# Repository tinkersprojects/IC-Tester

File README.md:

# IC Tester
[https://tinkersprojects.com/](https://tinkersprojects.com/)

This is an IC tester for any type of logic chip. The device pules every pin combination and reads the all other pins to find which type of chip it is. The chip would have been already analysed before testing.

To read a 28 pin chip would take about 1/2 days and Thisbe is why I made the device be able to select the number pins of the chip to Be Tested. The larger the number of pins the slower it will read.

The device USB a sheld that attaches to an Arduino mega development board. The sheld has an LCD, SD and a user interface as well as the chip reader. To test the chip, the device uses 5v from the Arduino.

The PCB can be purchased from https://tinkersprojects.com/product/ic-tester/

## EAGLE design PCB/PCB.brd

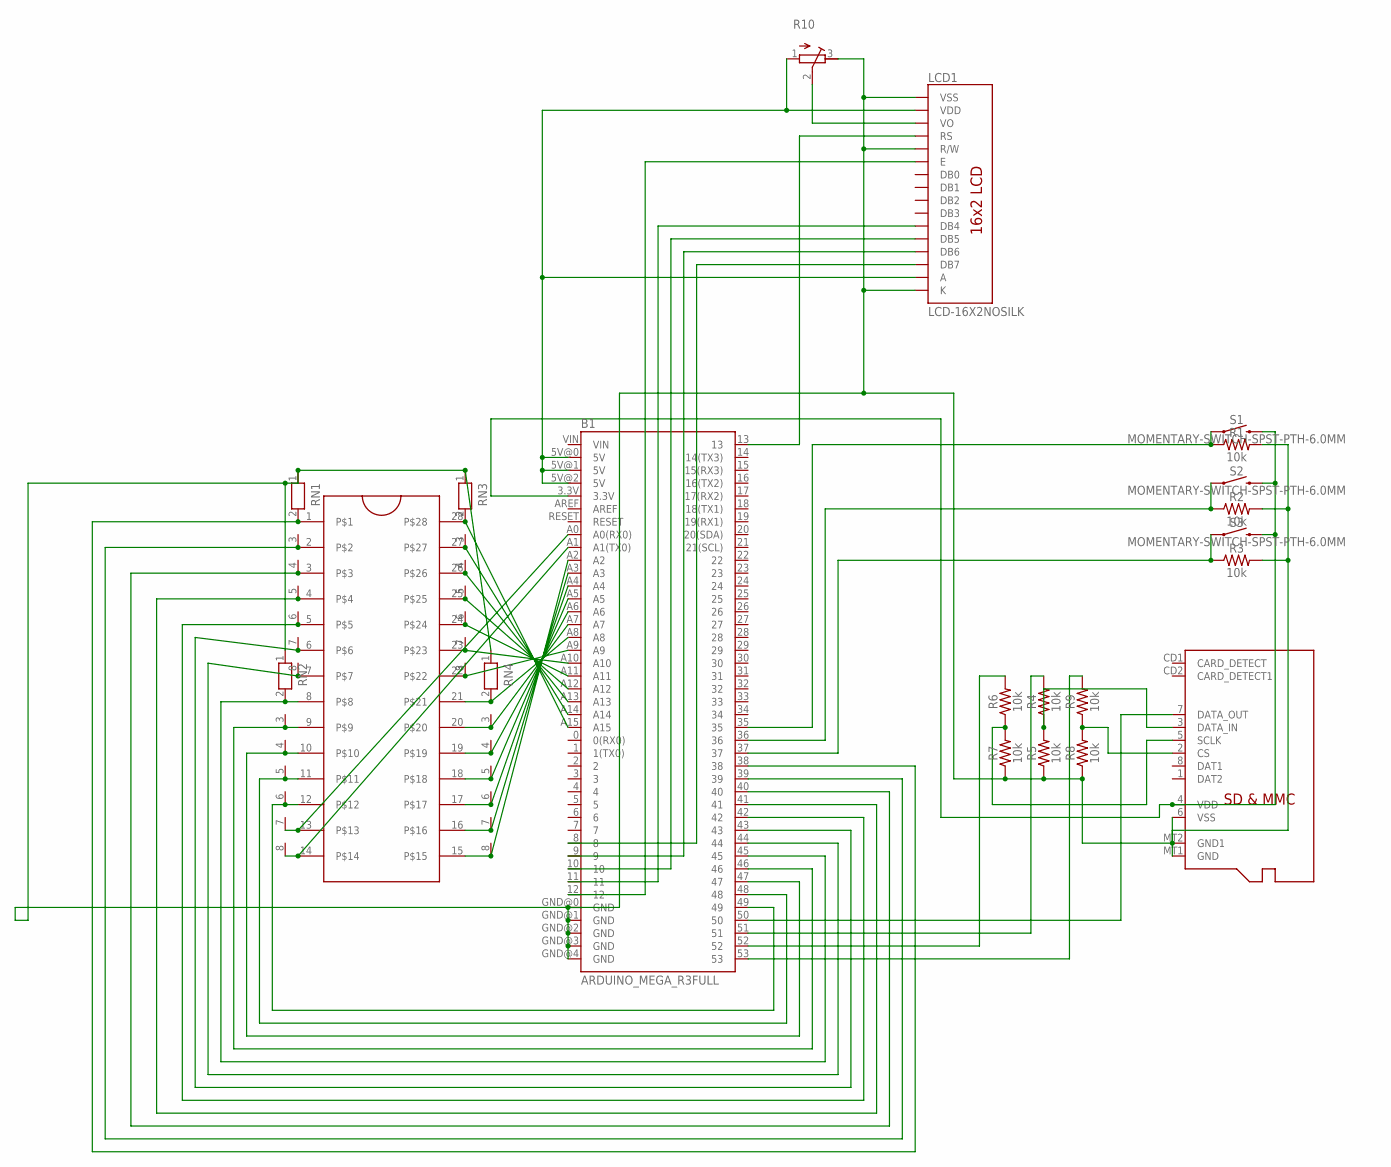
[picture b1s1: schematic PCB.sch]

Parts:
B1: ARDUINO_MEGA_R3FULL; ARDUINO_MEGA
LCD1: LCD-16X2NOSILK; LCD-16X2_NOSILK
R1, R2, R3, R4, R5, R6, R7, R8, R9: 10k; AXIAL-0.3
R10: R-TRIMM3339P; RTRIM3339P
RN1, RN2, RN3, RN4: RN07; RN-8
S1, S2, S3: MOMENTARY-SWITCH-SPST-PTH-6.0MM; TACTILE_SWITCH_PTH_6.0MM
U$1: MICROSD
U$2: ZIFSOCKET-28-3ZIFFSOCKET-28-3; DIL28-3-ZIF_SOCKET

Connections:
unnamed: B1.A15, RN3.2, U$2.28
unnamed: B1.A14, RN3.3, U$2.27
unnamed: B1.A13, RN3.4, U$2.26
unnamed: B1.A12, RN3.5, U$2.25
unnamed: B1.A11, RN3.6, U$2.24
unnamed: B1.A10, RN3.7, U$2.23
unnamed: B1.A9, RN3.8, U$2.22
unnamed: B1.A8, RN4.2, U$2.21
unnamed: B1.A7, RN4.3, U$2.20
unnamed: B1.A6, RN4.4, U$2.19
unnamed: B1.A5, RN4.5, U$2.18
unnamed: B1.A4, RN4.6, U$2.17
unnamed: B1.A3, RN4.7, U$2.16
unnamed: B1.A2, RN4.8, U$2.15
unnamed: B1.A1 (A1(TX0)), RN2.8, U$2.14
unnamed: B1.A0 (A0(RX0)), RN2.7, U$2.13
unnamed: B1.49, RN2.6, U$2.12
unnamed: B1.48, RN2.5, U$2.11
unnamed: B1.47, RN2.4, U$2.10
unnamed: B1.46, RN2.3, U$2.9
unnamed: B1.45, RN2.2, U$2.8
unnamed: B1.44, RN1.8, U$2.7
unnamed: B1.43, RN1.7, U$2.6
unnamed: B1.42, RN1.6, U$2.5
unnamed: B1.41, RN1.5, U$2.4
unnamed: B1.40, RN1.4, U$2.3
unnamed: B1.39, RN1.3, U$2.2
unnamed: B1.38, RN1.2, U$2.1
unnamed: B1.37, R3.P$1 (1), S3.1
unnamed: B1.5V@0 (5V), B1.5V@1 (5V), B1.5V@2 (5V), LCD1.2 (VDD), LCD1.15 (A), R10.1 (A)
unnamed: R6.P$1 (1), R7.P$2 (2), U$1.5 (SCLK)
unnamed: R8.P$2 (2), R9.P$1 (1), U$1.2 (CS)
unnamed: LCD1.3 (VO), R10.2 (S)
unnamed: B1.50, U$1.7 (DATA_OUT)
unnamed: R4.P$1 (1), R5.P$2 (2), U$1.3 (DATA_IN)
unnamed: B1.51, R4.P$2 (2)
unnamed: B1.53, R9.P$2 (2)
unnamed: B1.52, R6.P$2 (2)
unnamed: B1.13, LCD1.4 (RS)
unnamed: B1.12, LCD1.6 (E)
unnamed: B1.11, LCD1.11 (DB4)
unnamed: B1.10, LCD1.12 (DB5)
unnamed: B1.9, LCD1.13 (DB6)
unnamed: B1.8, LCD1.14 (DB7)
unnamed: B1.36, R2.P$1 (1), S2.1
unnamed: B1.35, R1.P$1 (1), S1.1
VDD: B1.3.3V, S1.3 (2), S2.3 (2), S3.3 (2), U$1.4 (VDD)
VSS: B1.GND@0 (GND), B1.GND@1 (GND), B1.GND@2 (GND), B1.GND@3 (GND), B1.GND@4 (GND), LCD1.1 (VSS), LCD1.5 (R/W), LCD1.16 (K), R1.P$2 (2), R2.P$2 (2), R3.P$2 (2), R5.P$1 (1), R7.P$1 (1), R8.P$1 (1), R10.3 (E), RN1.1, RN2.1, RN3.1, RN4.1, U$1.6 (VSS), U$1.MT1 (GND), U$1.MT2 (GND1)

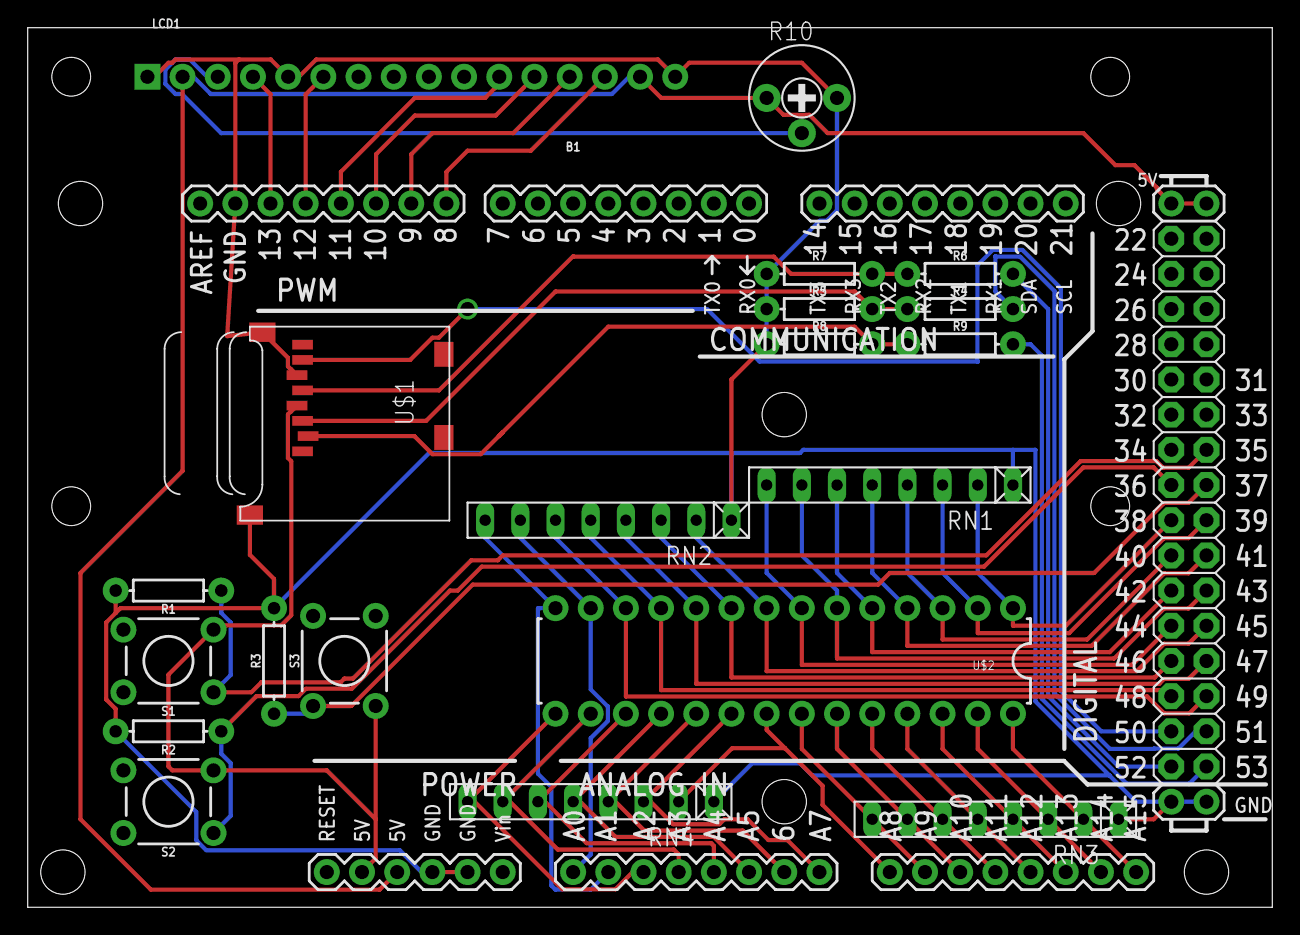
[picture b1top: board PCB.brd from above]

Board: 2 copper layers, 89.8 x 63.5 mm, 21 parts (0 on the bottom side), 48 nets.

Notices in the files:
parts and their libraries:
SparkFun-Boards: Licensing: Creative Commons ShareAlike 4.0 International - https://creativecommons.org/licenses/by-sa/4.0
